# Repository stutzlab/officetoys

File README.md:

# cozme
Peça na mesa e receba direto da cozinha

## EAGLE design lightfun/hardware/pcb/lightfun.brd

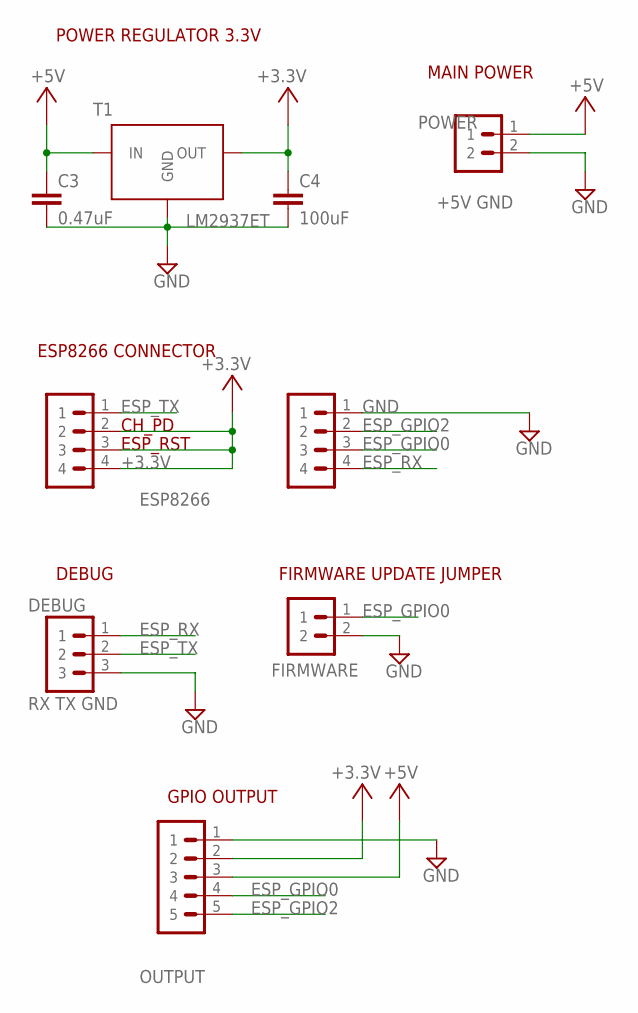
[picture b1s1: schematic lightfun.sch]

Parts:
C3: 0.47uF; C2.5-2; MPN 1C10Z5U104M050B
C4: 100uF; C2.5-2; MPN FK18X5R0J106M
DEBUG: RX TX GND; PIN-HEADER-3PIN
FIRMWARE: FIRMWARE; PIN-HEADER-2PIN
OUTPUT: GND 3.3V 5V IO0 IO2; PIN-HEADER-5PIN
P1: ESP8266; PIN-HEADER-4PIN
P2: ESP8266 CONNECTOR; PIN-HEADER-4PIN
POWER: +5V GND; PIN-HEADER-2PIN
T1: LM2937ET; TO-220; MPN LM2937ET-3.3

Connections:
+3.3V: C4.1, OUTPUT.2, P1.2, P1.3, P1.4, T1.OUTPUT (OUT)
+5V: C3.1, OUTPUT.3, POWER.1, T1.INPUT (IN)
ESP_GPIO0: FIRMWARE.1, OUTPUT.4, P2.3
ESP_GPIO2: OUTPUT.5, P2.2
ESP_RX: DEBUG.1, P2.4
ESP_TX: DEBUG.2, P1.1
GND: C3.2, C4.2, DEBUG.3, FIRMWARE.2, OUTPUT.1, P2.1, POWER.2, T1.GND

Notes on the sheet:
POWER REGULATOR 3.3V
CH_PD
ESP_RST
DEBUG
MAIN POWER
ESP8266 CONNECTOR
FIRMWARE UPDATE JUMPER
GPIO OUTPUT

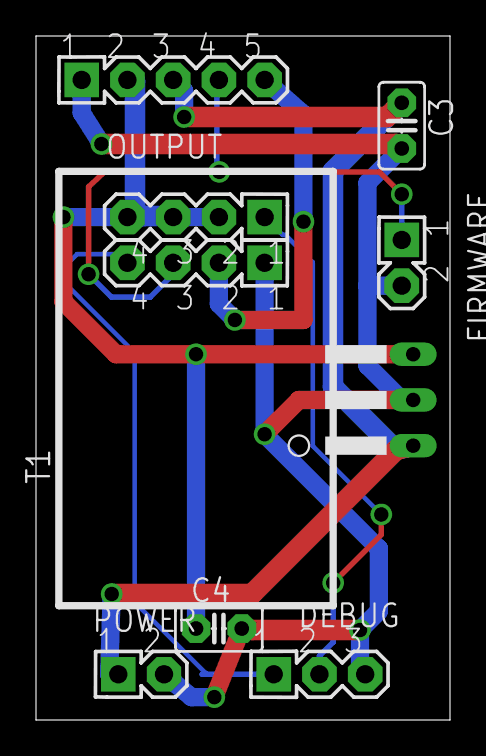
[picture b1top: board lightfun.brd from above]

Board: 2 copper layers, 23.0 x 38.0 mm, 9 parts (0 on the bottom side), 7 nets.

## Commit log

2016-04-04 Generic ESP8266 PCB routing
2016-04-21 PCB update
2016-04-29 Updated after lasercut printing
2016-05-06 Updated model
2016-05-07 Renamed to argibee
2016-05-07 Renamed to esp8266-nodemcu
2016-11-30 updated argibee
